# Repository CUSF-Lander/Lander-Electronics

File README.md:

# Lander-Electronics
Electronics for 25kg TVC hopper

### Creating new projects:
Open ```Template Project/Template Project.kicad_pro``` <br>
File>Save_As, then enter the new filename

### Adding New Symbols and Footprints
Adding footprints and symbols to the project specific library is the same as  usual. When connecting a footprint to a .stp file define a relative path to the file using ```${KIPRJMOD}/../Symbols and Footprints/3D Models/FILENAME.stp```

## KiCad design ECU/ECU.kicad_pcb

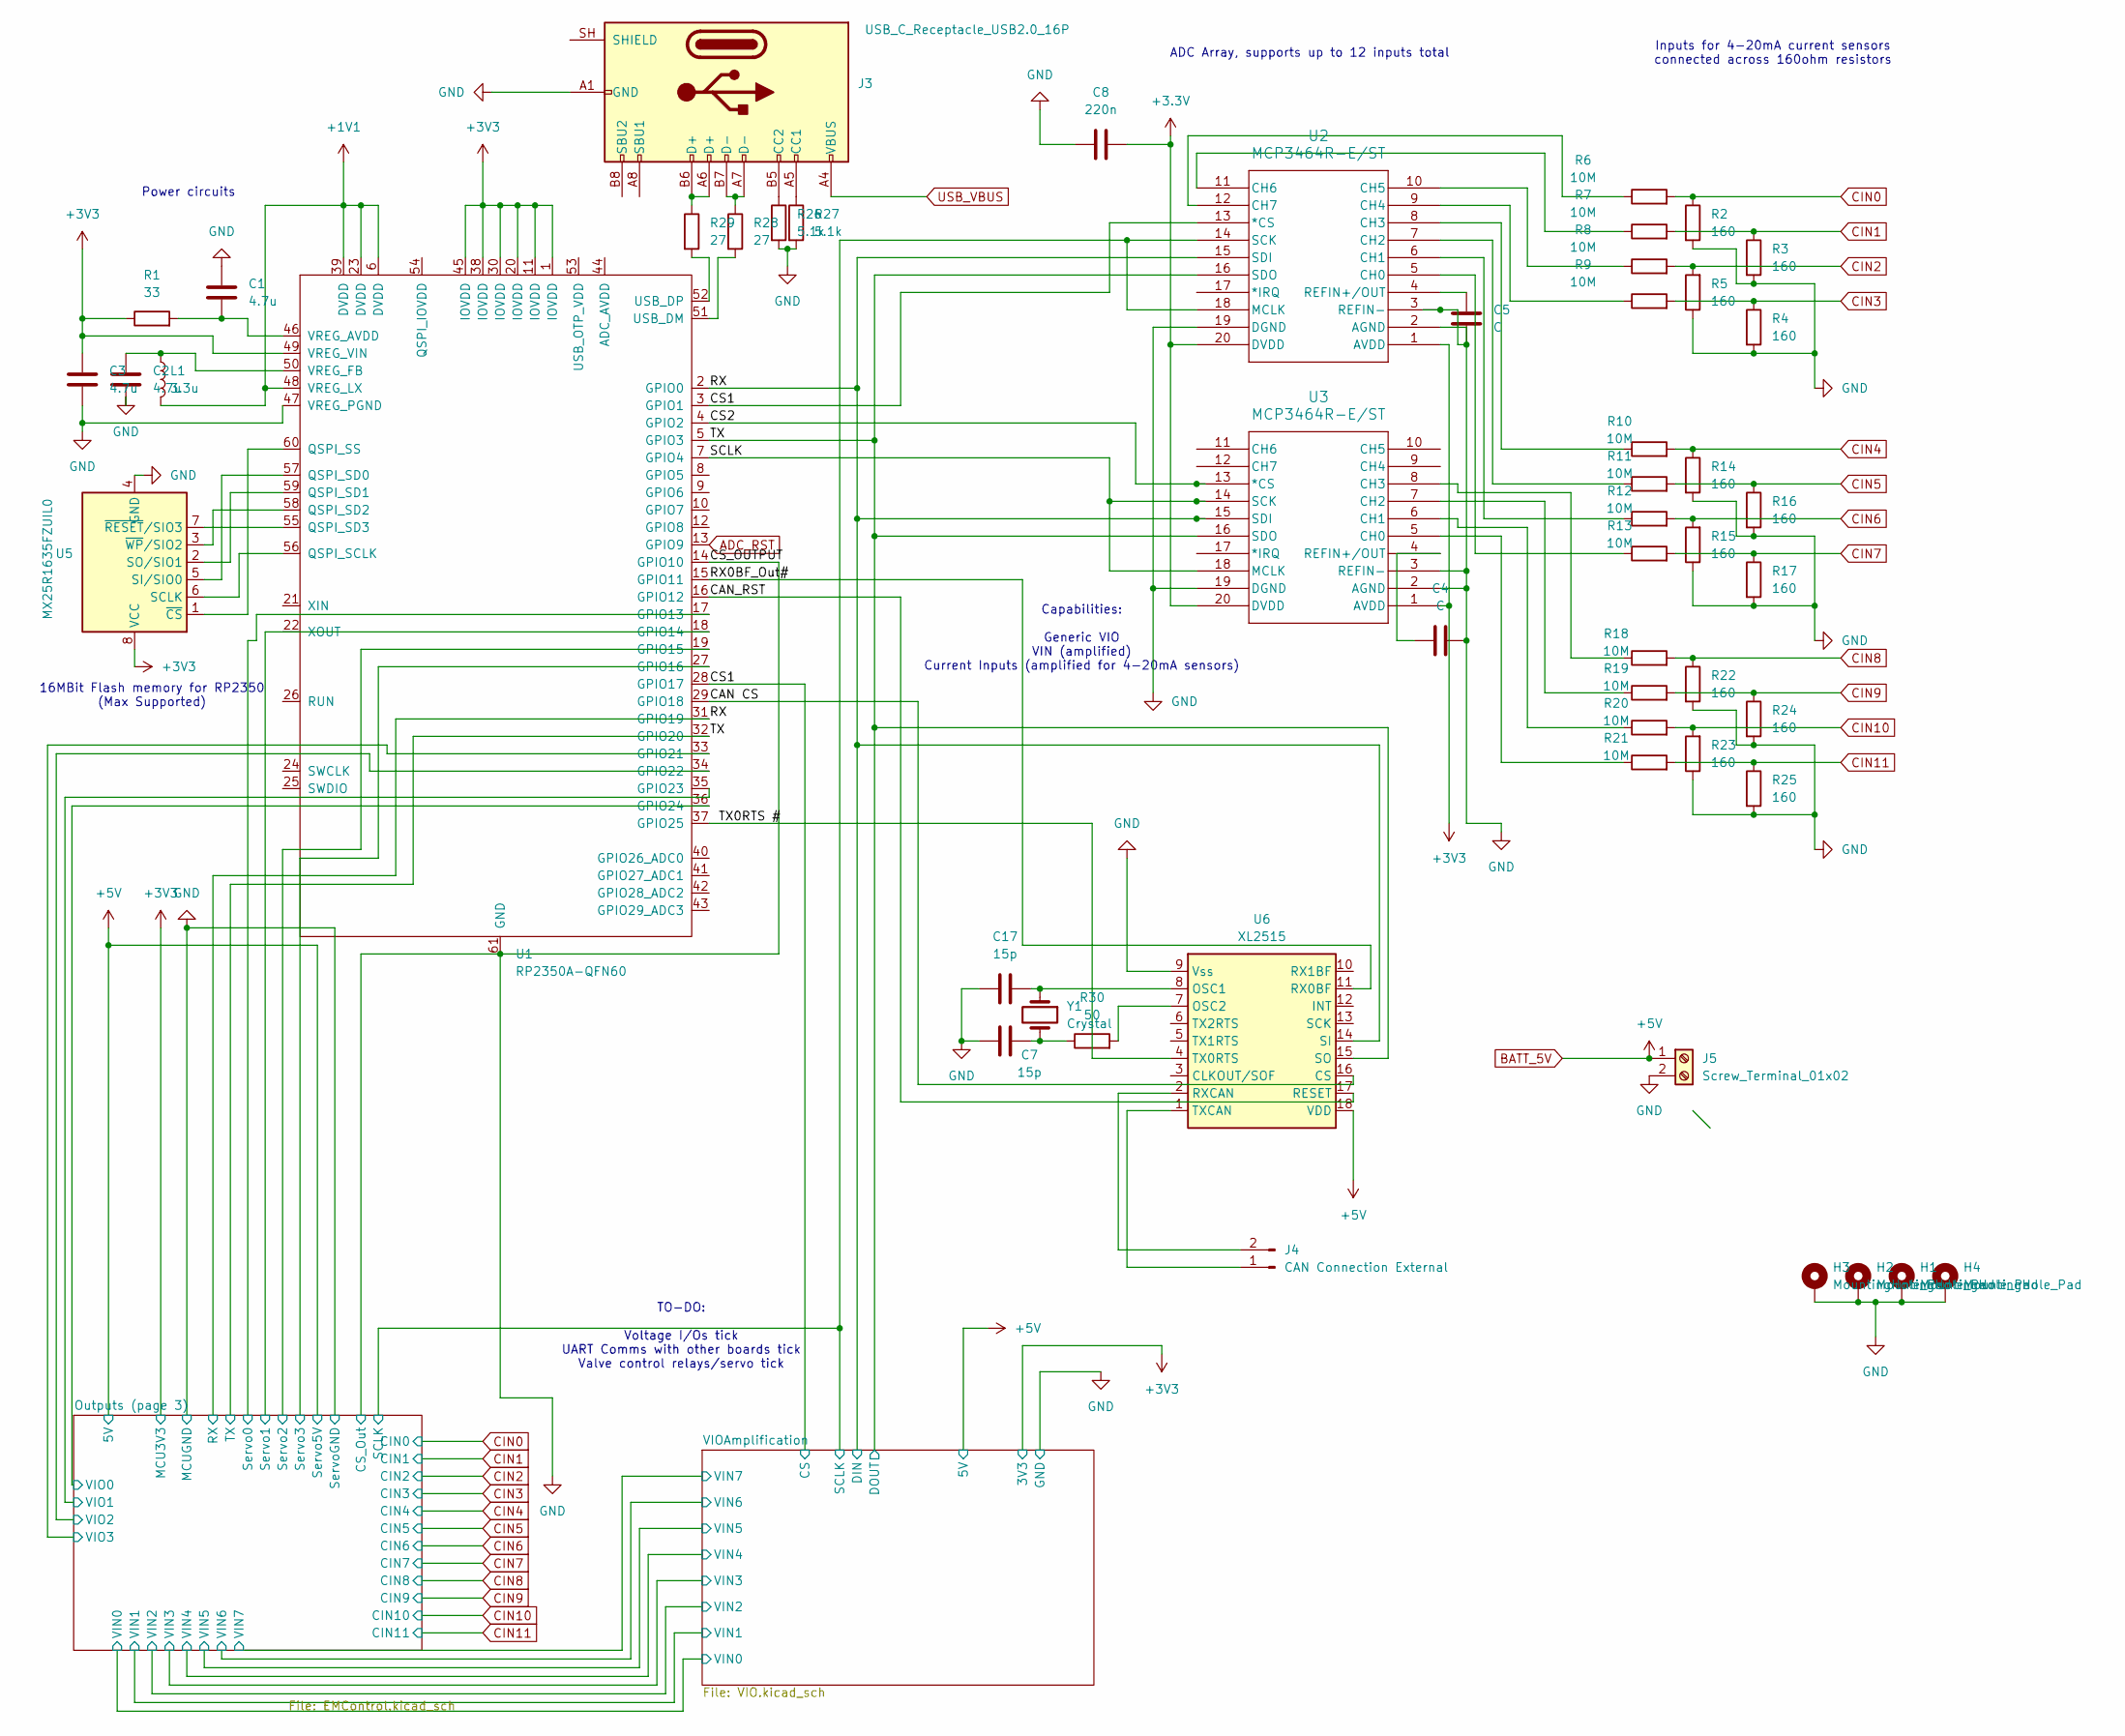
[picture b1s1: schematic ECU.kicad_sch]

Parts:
C1, C2, C3: 4.7u; C_1206_3216Metric_Pad1.33x1.80mm_HandSolder
C4, C5: C; C_1206_3216Metric
C7, C17: 15p; C_1206_3216Metric_Pad1.33x1.80mm_HandSolder
C8: 220n; C_0805_2012Metric_Pad1.18x1.45mm_HandSolder
H1, H2, H3, H4: MountingHole_Pad; MountingHole_3.2mm_M3_DIN965_Pad_TopBottom
J3: USB_C_Receptacle_USB2.0_16P; USB_C_Receptacle_HRO_TYPE-C-31-M-12
J4: CAN Connection External; PinHeader_1x02_P2.54mm_Vertical
J5: Screw_Terminal_01x02; TerminalBlock_Xinya_XY308-2.54-2P_1x02_P2.54mm_Horizontal
L1: 3.3u; L_0805_2012Metric_Pad1.05x1.20mm_HandSolder
R1: 33; R_1206_3216Metric_Pad1.30x1.75mm_HandSolder
R2, R3, R4, R5, R14, R15, R16, R17, R22, R23, R24, R25: 160; R_0805_2012Metric_Pad1.20x1.40mm_HandSolder
R6, R7, R8, R9, R10, R11, R12, R13, R18, R19, R20, R21: 10M; R_0805_2012Metric_Pad1.20x1.40mm_HandSolder
R26, R27: 5.1k; R_0805_2012Metric_Pad1.20x1.40mm_HandSolder
R28, R29: 27; R_0805_2012Metric_Pad1.20x1.40mm_HandSolder
R30: 50; R_1206_3216Metric_Pad1.30x1.75mm_HandSolder
U1: RP2350A-QFN60; QFN-60-1EP_7x7mm_P0.4mm_EP3.4x3.4mm
U2, U3: MCP3464R-E/ST; TSSOP-20_4.4x6.5mm_P0.4mm
U5: MX25R1635FZUIL0; JEITA_SOIC-8_3.9x4.9mm_P1.27mm
U6: XL2515; SOP-18_7.495x11.515mm_P1.27mm
Y1: Crystal; Crystal_HC49-U_Vertical

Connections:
+1V1: L1.2, U1.6 (DVDD), U1.23 (DVDD), U1.39 (DVDD), U1.48 (VREG_LX)
+3.3V: C8.2, U2.20 (DVDD), U3.20 (DVDD)
+3V3: C3.1, R1.1, U1.1 (IOVDD), U1.11 (IOVDD), U1.20 (IOVDD), U1.30 (IOVDD), U1.38 (IOVDD), U1.45 (IOVDD), U1.49 (VREG_VIN), U2.1 (AVDD), U3.1 (AVDD), U5.8 (VCC); also elsewhere on the board
/CAN CS: U1.29 (GPIO18), U6.16 (CS)
/CAN_RST: U1.16 (GPIO12), U6.17 (RESET)
/CS1: U1.3 (GPIO1), U1.28 (GPIO17), U2.13 (*CS); also elsewhere on the board
/CS2: U1.4 (GPIO2), U3.13 (*CS)
/Outputs (page 3)/SCLK: U2.14 (SCK), U2.18 (MCLK); also elsewhere on the board
/Outputs (page 3)/Servo0: U1.17 (GPIO13); also elsewhere on the board
/Outputs (page 3)/Servo1: U1.18 (GPIO14); also elsewhere on the board
/Outputs (page 3)/Servo2: U1.19 (GPIO15); also elsewhere on the board
/Outputs (page 3)/Servo3: U1.27 (GPIO16); also elsewhere on the board
/Outputs (page 3)/VIO0: U1.36 (GPIO24); also elsewhere on the board
/Outputs (page 3)/VIO1: U1.35 (GPIO23); also elsewhere on the board
/Outputs (page 3)/VIO2: U1.34 (GPIO22); also elsewhere on the board
/Outputs (page 3)/VIO3: U1.33 (GPIO21); also elsewhere on the board
/RX: U1.2 (GPIO0), U1.31 (GPIO19), U2.15 (SDI), U3.15 (SDI), U6.14 (SI); also elsewhere on the board
/RX0BF_Out#: U1.15 (GPIO11), U6.11 (RX0BF)
/SCLK: U1.7 (GPIO4), U3.14 (SCK), U3.18 (MCLK)
/TX: U1.5 (GPIO3), U1.32 (GPIO20), U2.16 (SDO), U3.16 (SDO), U6.15 (SO); also elsewhere on the board
/TX0RTS #: U1.37 (GPIO25), U6.4 (TX0RTS)
ADC_RST: U1.13 (GPIO9)
BATT_5V: J5.1, U6.18 (VDD); also elsewhere on the board
CIN0: R2.1, R6.2; also elsewhere on the board
CIN1: R3.1, R7.2; also elsewhere on the board
CIN2: R5.2, R8.2; also elsewhere on the board
CIN3: R4.1, R9.2; also elsewhere on the board
CIN4: R10.2, R14.1; also elsewhere on the board
CIN5: R11.2, R16.1; also elsewhere on the board
CIN6: R12.2, R15.2; also elsewhere on the board
CIN7: R13.2, R17.1; also elsewhere on the board
CIN8: R18.2, R22.1; also elsewhere on the board
CIN9: R19.2, R24.1; also elsewhere on the board
CIN10: R20.2, R23.2; also elsewhere on the board
CIN11: R21.2, R25.1; also elsewhere on the board
GND: C1.1, C2.2, C3.2, C4.1, C5.2, C7.1, C8.1, C17.1, H1.1 (1_1), H2.1 (1_1), H3.1 (1_1), H4.1 (1_1), J3.A1 (GND), J3.A12 (GND), J3.B1 (GND), J3.B12 (GND), J5.2, R2.2, R3.2, R4.2, R5.1, R14.2, R15.1, R16.2, R17.2, R22.2, R23.1, R24.2, R25.2, R26.2, R27.2, U1.14 (GPIO10), U1.47 (VREG_PGND), U1.61 (GND), U2.2 (AGND), U2.3 (REFIN-), U2.19 (DGND), U3.2 (AGND), U3.3 (REFIN-), U3.19 (DGND), U5.4 (GND), U6.9 (Vss); also elsewhere on the board
unnamed: C7.2, R30.1, Y1.2
unnamed: J3.A5 (CC1), R27.1
unnamed: J3.B5 (CC2), R26.1
unnamed: J3.A6 (D+), J3.B6 (D+), R29.1
unnamed: J3.A7 (D-), J3.B7 (D-), R28.1
unnamed: J4.1, U6.1 (TXCAN)
unnamed: J4.2, U6.2 (RXCAN)
unnamed: U1.56 (QSPI_SCLK), U5.6 (SCLK)
unnamed: U1.57 (QSPI_SD0), U5.5 (SI/SIO0)
unnamed: U1.59 (QSPI_SD1), U5.2 (SO/SIO1)
unnamed: U1.58 (QSPI_SD2), U5.3 (~WP/SIO2)
unnamed: U1.55 (QSPI_SD3), U5.7 (~RESET/SIO3)
unnamed: U1.60 (QSPI_SS), U5.1 (~CS)
unnamed: R28.2, U1.51 (USB_DM)
unnamed: R29.2, U1.52 (USB_DP)
unnamed: C1.2, R1.2, U1.46 (VREG_AVDD)
unnamed: C2.1, L1.1, U1.50 (VREG_FB)
unnamed: R13.1, U2.5 (CH0)
unnamed: R12.1, U2.6 (CH1)
unnamed: R11.1, U2.7 (CH2)
unnamed: R10.1, U2.8 (CH3)
unnamed: R9.1, U2.9 (CH4)
unnamed: R8.1, U2.10 (CH5)
unnamed: R7.1, U2.11 (CH6)
unnamed: R6.1, U2.12 (CH7)
unnamed: C5.1, U2.4 (REFIN+/OUT)
unnamed: R21.1, U3.5 (CH0)
unnamed: R20.1, U3.6 (CH1)
unnamed: R19.1, U3.7 (CH2)
unnamed: R18.1, U3.8 (CH3)
unnamed: C4.2, U3.4 (REFIN+/OUT)
unnamed: C17.2, U6.8 (OSC1), Y1.1
unnamed: R30.2, U6.7 (OSC2)
USB_VBUS: J3.A4 (VBUS), J3.A9 (VBUS), J3.B4 (VBUS), J3.B9 (VBUS); also elsewhere on the board

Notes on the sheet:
ADC Array, supports up to 12 inputs total
Capabilities: Generic VIO VIN (amplified) Current Inputs (amplified for 4-20mA sensors)
Power circuits
Inputs for 4-20mA current sensors connected across 160ohm resistors
TO-DO: Voltage I/Os tick UART Comms with other boards tick Valve control relays/servo tick
16MBit Flash memory for RP2350 (Max Supported)

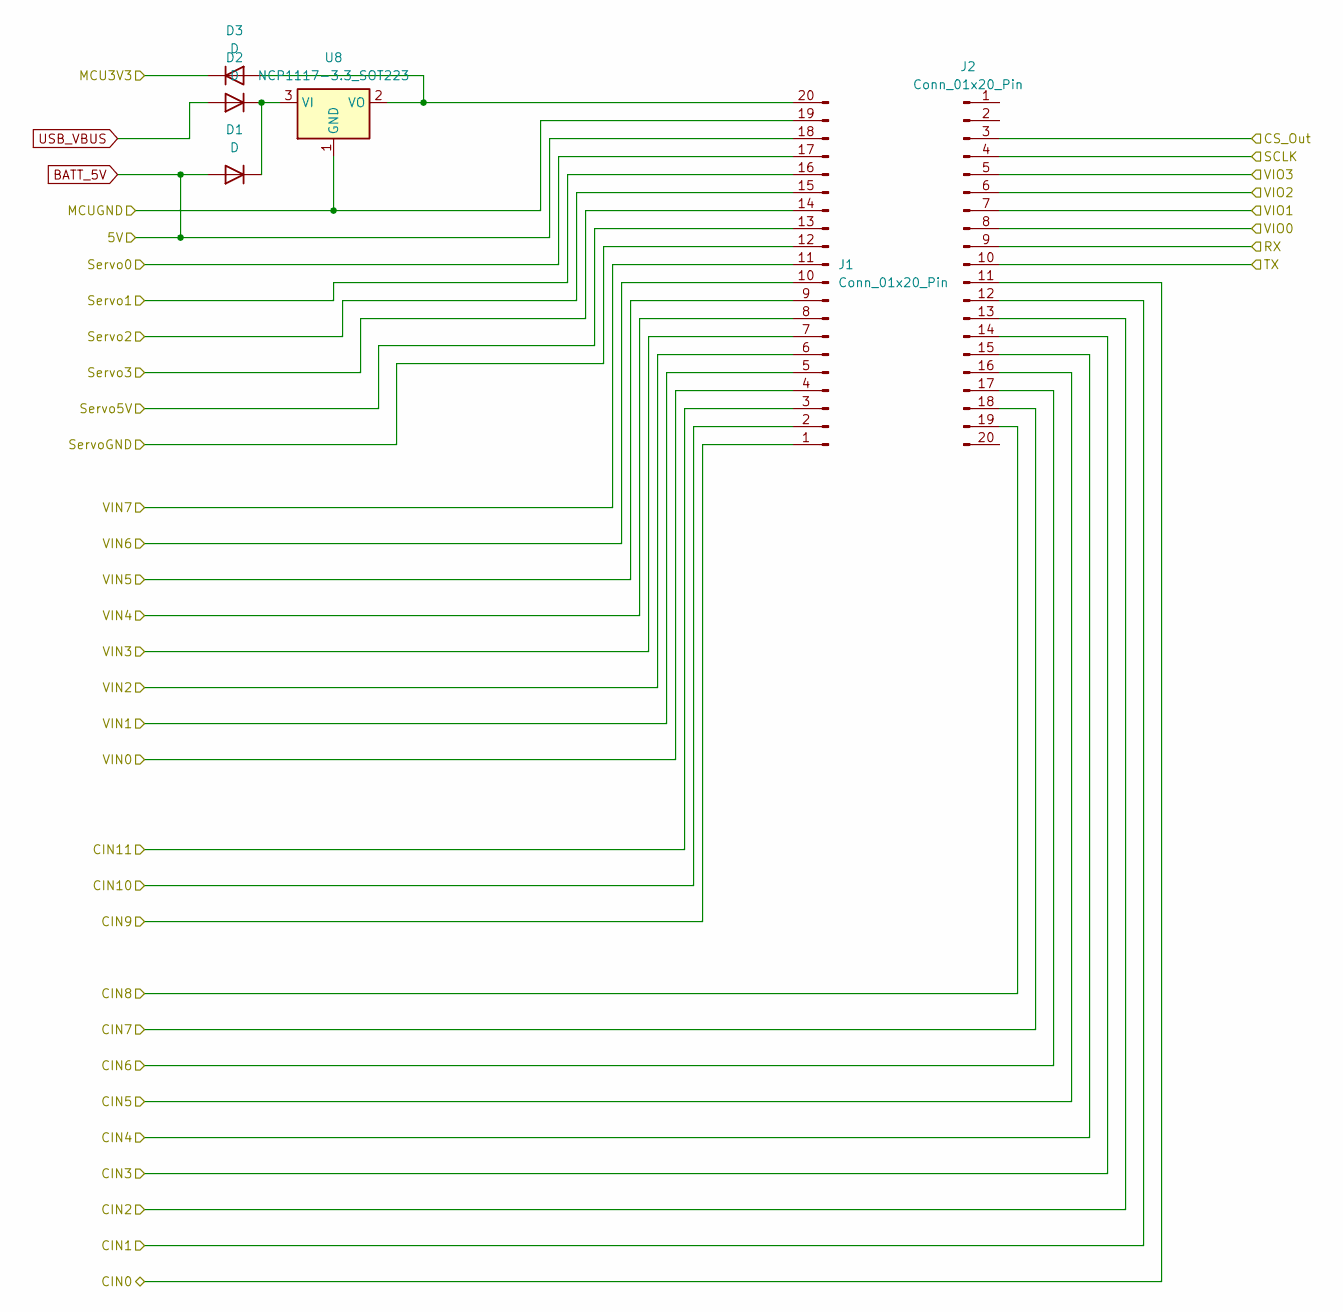
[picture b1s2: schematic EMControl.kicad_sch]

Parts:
D1, D2, D3: D; D_1206_3216Metric_Pad1.42x1.75mm_HandSolder
J1, J2: Conn_01x20_Pin; PinHeader_1x20_P1.00mm_Vertical
U8: NCP1117-3.3_SOT223; SOT-223-3_TabPin2

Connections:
+3V3: D3.1 (K); also elsewhere on the board
/Outputs (page 3)/SCLK: J2.4; also elsewhere on the board
/Outputs (page 3)/Servo0: J1.17; also elsewhere on the board
/Outputs (page 3)/Servo1: J1.16; also elsewhere on the board
/Outputs (page 3)/Servo2: J1.15; also elsewhere on the board
/Outputs (page 3)/Servo3: J1.14; also elsewhere on the board
/Outputs (page 3)/VIN0: J1.4; also elsewhere on the board
/Outputs (page 3)/VIN1: J1.5; also elsewhere on the board
/Outputs (page 3)/VIN2: J1.6; also elsewhere on the board
/Outputs (page 3)/VIN3: J1.7; also elsewhere on the board
/Outputs (page 3)/VIN4: J1.8; also elsewhere on the board
/Outputs (page 3)/VIN5: J1.9; also elsewhere on the board
/Outputs (page 3)/VIN6: J1.10; also elsewhere on the board
/Outputs (page 3)/VIN7: J1.11; also elsewhere on the board
/Outputs (page 3)/VIO0: J2.8; also elsewhere on the board
/Outputs (page 3)/VIO1: J2.7; also elsewhere on the board
/Outputs (page 3)/VIO2: J2.6; also elsewhere on the board
/Outputs (page 3)/VIO3: J2.5; also elsewhere on the board
/RX: J2.9; also elsewhere on the board
/TX: J2.10; also elsewhere on the board
BATT_5V: D1.2 (A), J1.13, J1.18; also elsewhere on the board
CIN0: J2.11; also elsewhere on the board
CIN1: J2.12; also elsewhere on the board
CIN2: J2.13; also elsewhere on the board
CIN3: J2.14; also elsewhere on the board
CIN4: J2.15; also elsewhere on the board
CIN5: J2.16; also elsewhere on the board
CIN6: J2.17; also elsewhere on the board
CIN7: J2.18; also elsewhere on the board
CIN8: J2.19; also elsewhere on the board
CIN9: J1.1; also elsewhere on the board
CIN10: J1.2; also elsewhere on the board
CIN11: J1.3; also elsewhere on the board
GND: J1.12, J1.19, J2.3, U8.1 (GND); also elsewhere on the board
unnamed: D1.1 (K), D2.1 (K), U8.3 (VI)
unnamed: D3.2 (A), J1.20, U8.2 (VO)
USB_VBUS: D2.2 (A); also elsewhere on the board

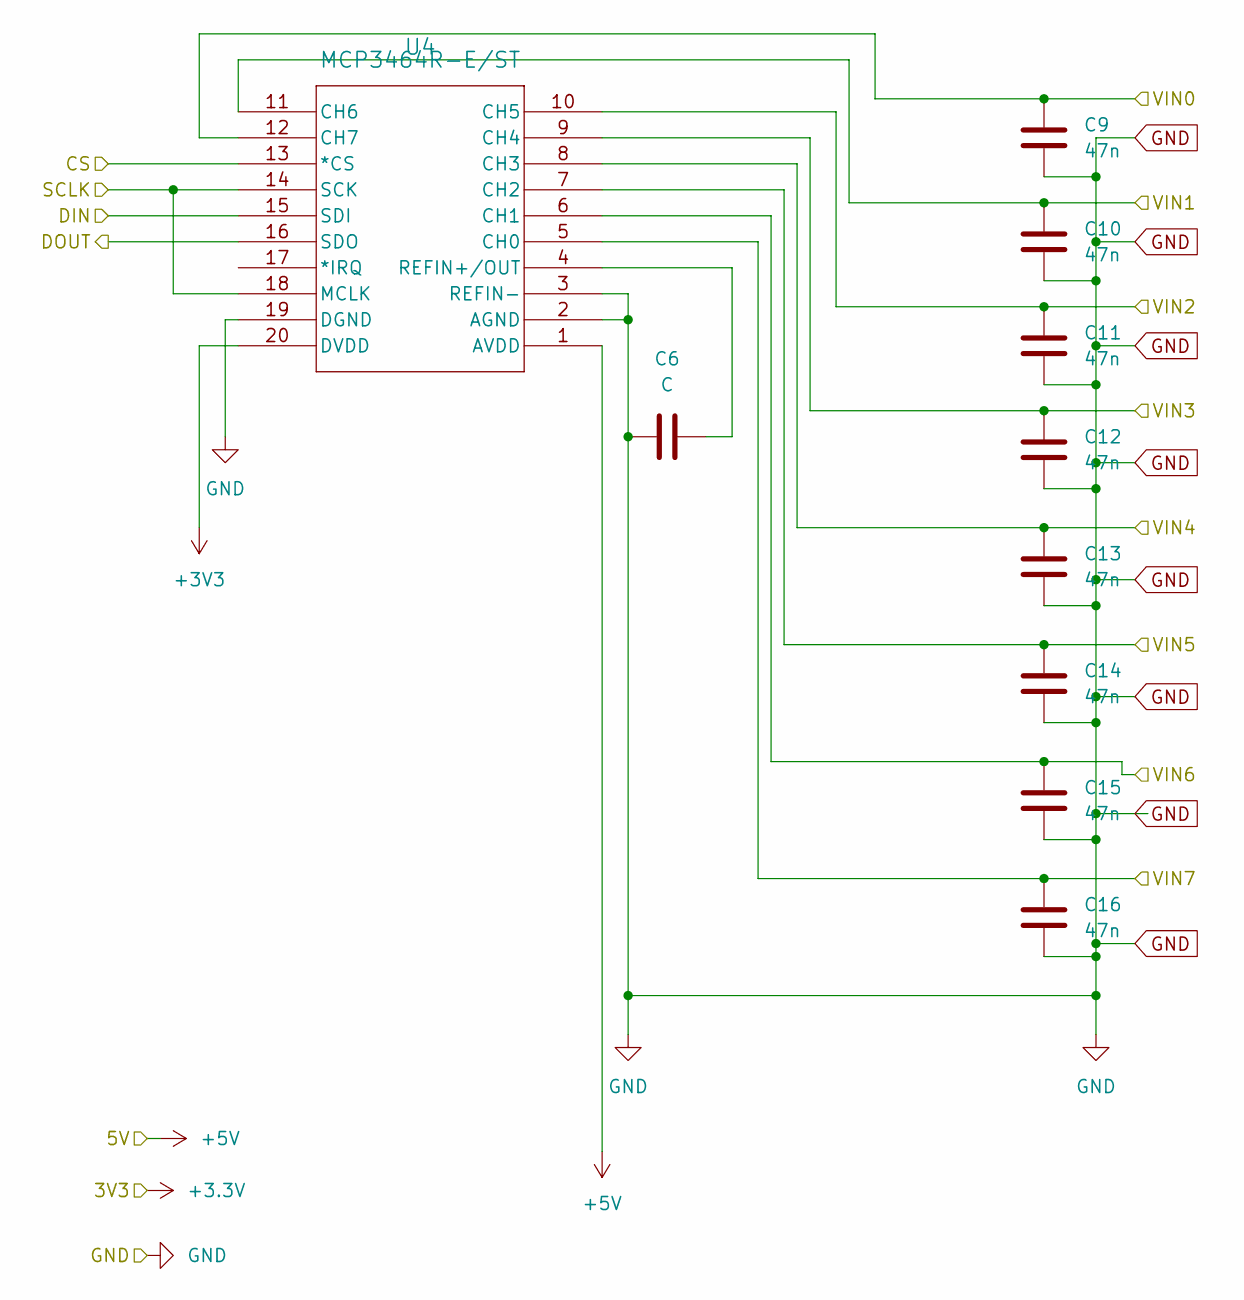
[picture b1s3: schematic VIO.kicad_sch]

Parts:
C6: C; C_0805_2012Metric
C9, C10, C11, C12, C13, C14, C15, C16: 47n; C_1206_3216Metric_Pad1.33x1.80mm_HandSolder
U4: MCP3464R-E/ST; TSSOP-20_4.4x6.5mm_P0.4mm

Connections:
+3V3: U4.20 (DVDD); also elsewhere on the board
/CS1: U4.13 (*CS); also elsewhere on the board
/Outputs (page 3)/SCLK: U4.14 (SCK), U4.18 (MCLK); also elsewhere on the board
/Outputs (page 3)/VIN0: C9.1, U4.12 (CH7); also elsewhere on the board
/Outputs (page 3)/VIN1: C10.1, U4.11 (CH6); also elsewhere on the board
/Outputs (page 3)/VIN2: C11.1, U4.10 (CH5); also elsewhere on the board
/Outputs (page 3)/VIN3: C12.1, U4.9 (CH4); also elsewhere on the board
/Outputs (page 3)/VIN4: C13.1, U4.8 (CH3); also elsewhere on the board
/Outputs (page 3)/VIN5: C14.1, U4.7 (CH2); also elsewhere on the board
/Outputs (page 3)/VIN6: C15.1, U4.6 (CH1); also elsewhere on the board
/Outputs (page 3)/VIN7: C16.1, U4.5 (CH0); also elsewhere on the board
/RX: U4.15 (SDI); also elsewhere on the board
/TX: U4.16 (SDO); also elsewhere on the board
BATT_5V: U4.1 (AVDD); also elsewhere on the board
GND: C6.2, C9.2, C10.2, C11.2, C12.2, C13.2, C14.2, C15.2, C16.2, U4.2 (AGND), U4.3 (REFIN-), U4.19 (DGND); also elsewhere on the board
unnamed: C6.1, U4.4 (REFIN+/OUT)

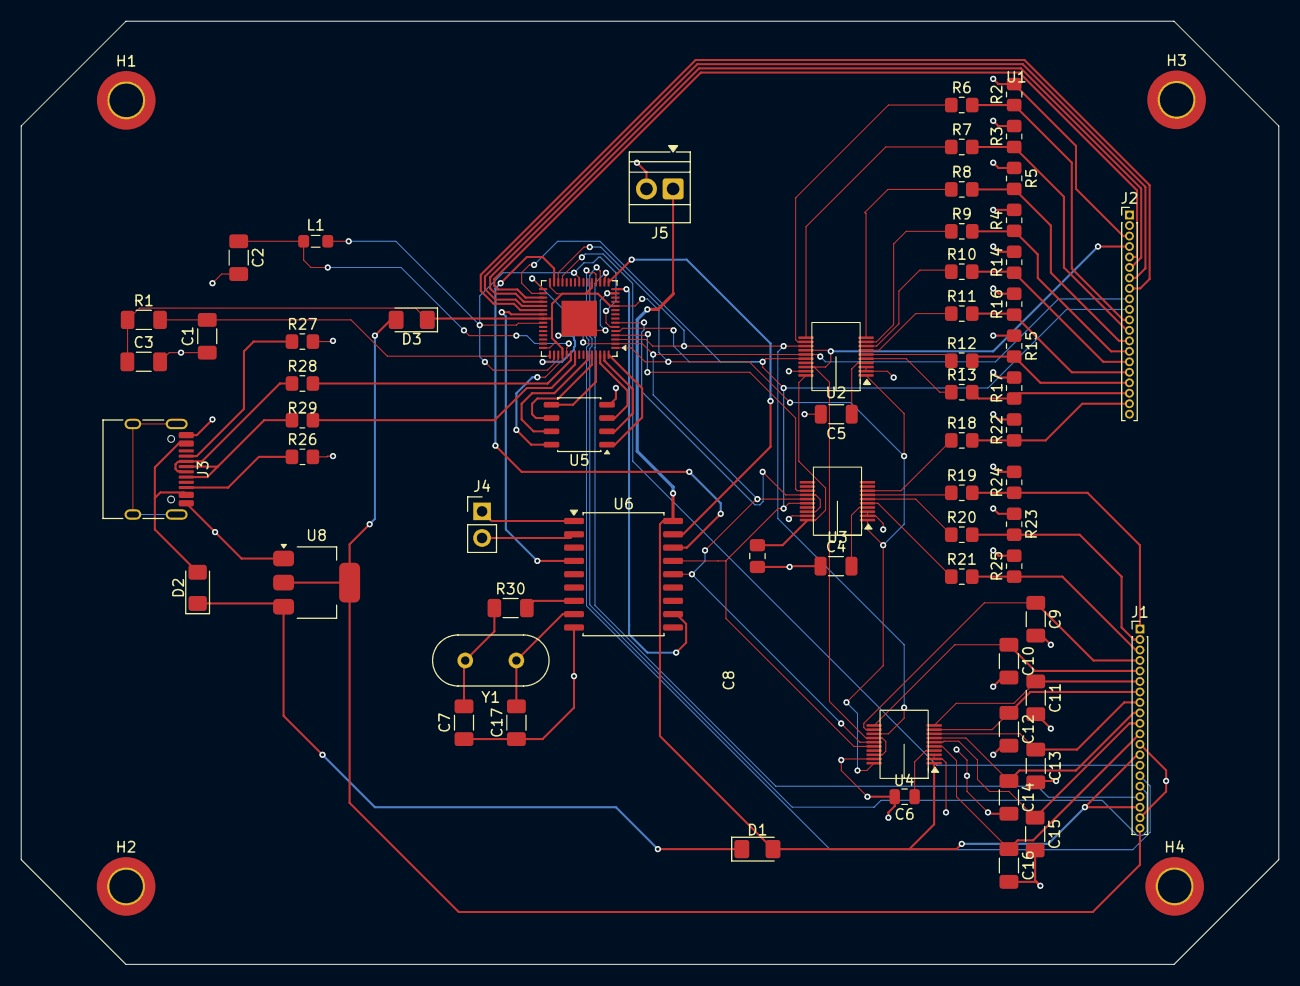
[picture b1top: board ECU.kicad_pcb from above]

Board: 2 copper layers, 120.0 x 90.0 mm, 68 parts (0 on the bottom side), 80 nets.

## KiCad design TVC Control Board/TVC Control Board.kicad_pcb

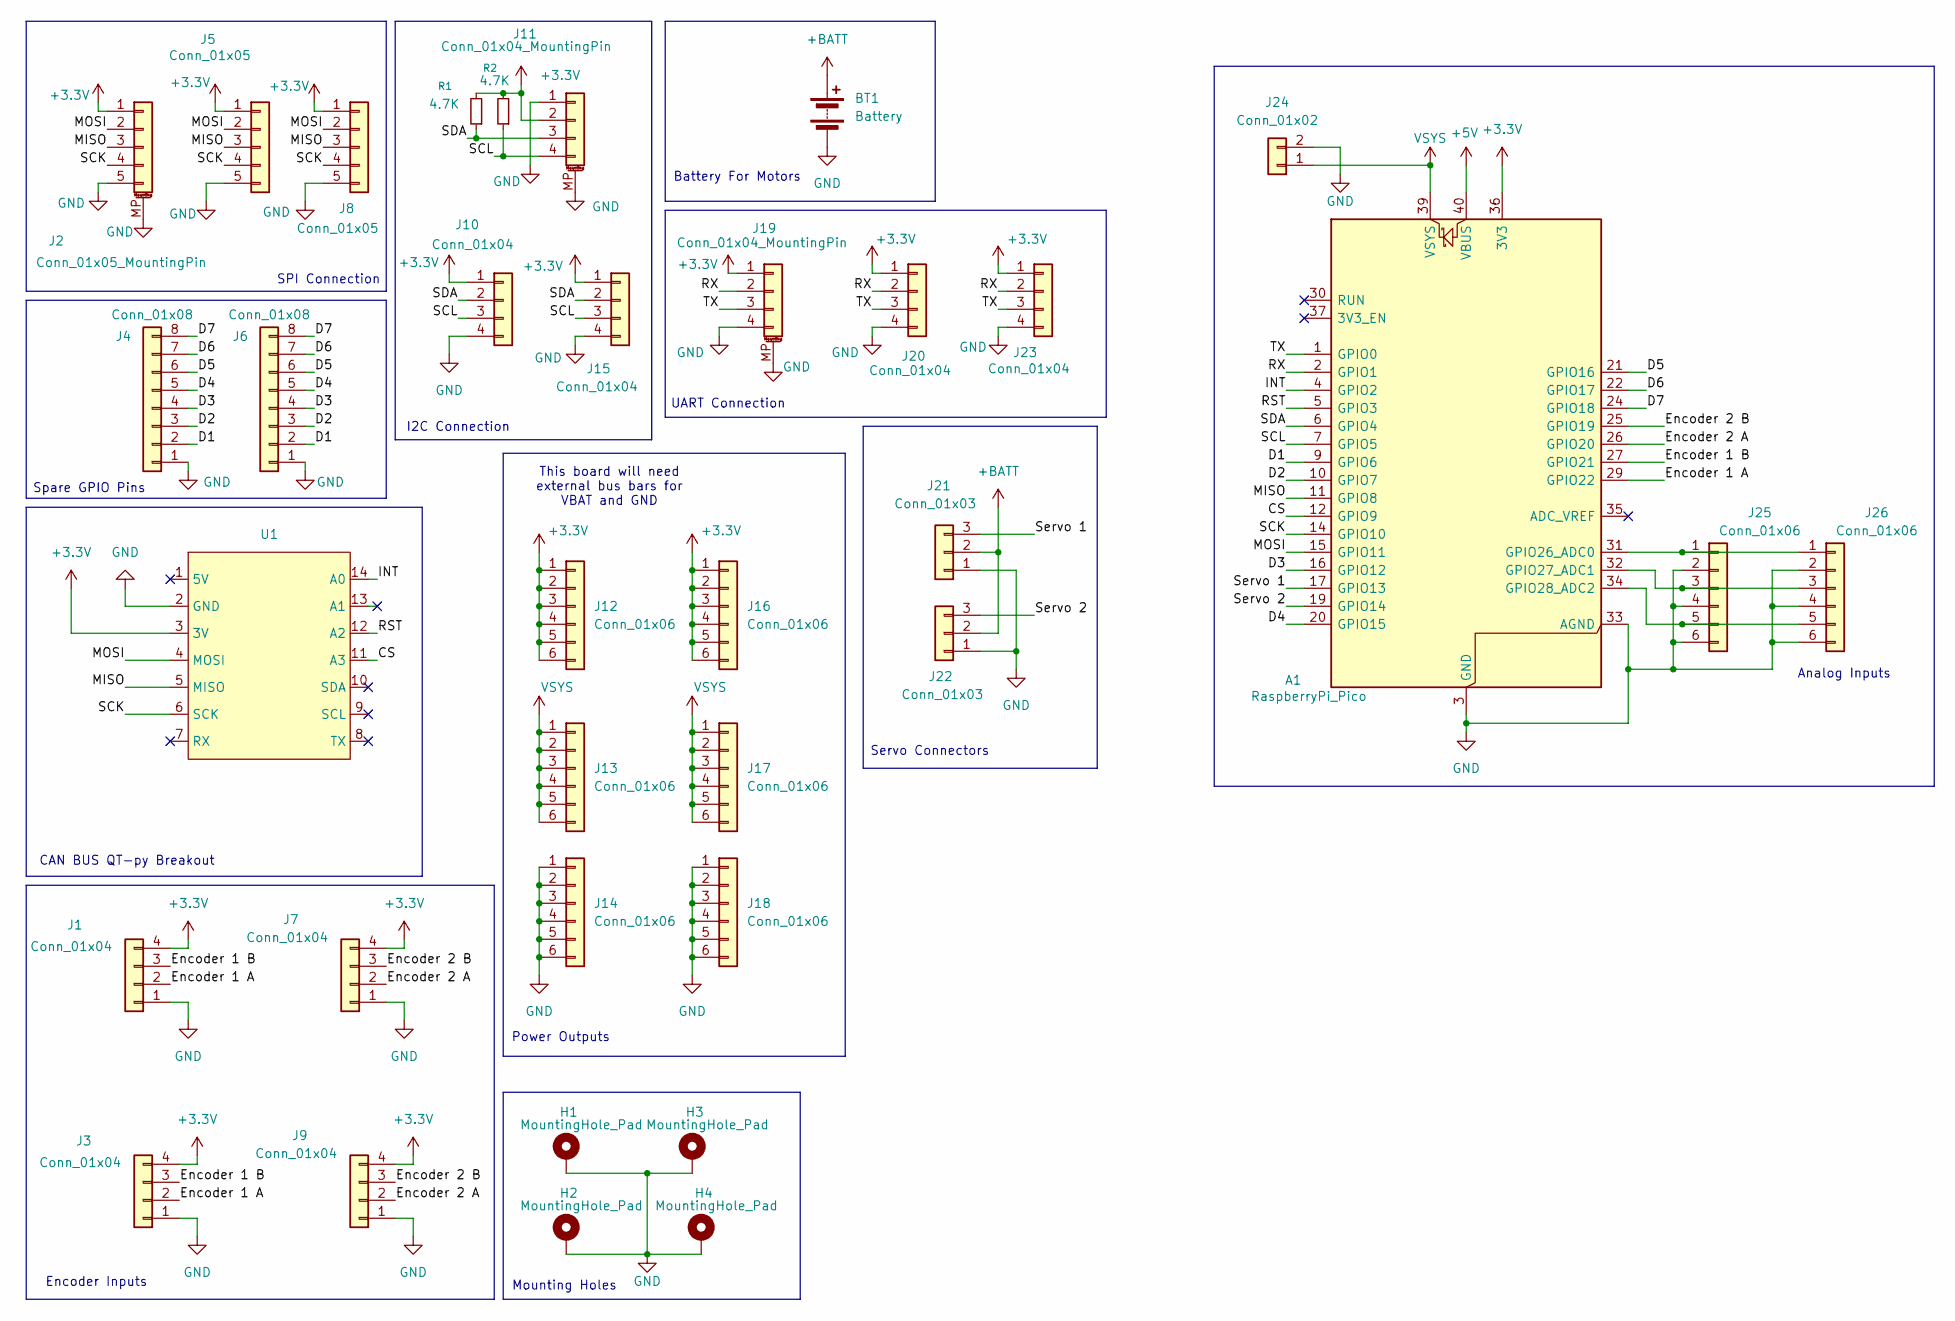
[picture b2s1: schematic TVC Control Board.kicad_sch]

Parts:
A1: RaspberryPi_Pico; RaspberryPi_Pico_Common_Unspecified
BT1: Battery; TVC Board Battery Connector
H1, H2, H3, H4: MountingHole_Pad; MountingHole_3.2mm_M3_Pad
J1, J3, J7, J9, J10, J15, J20, J23: Conn_01x04; PinHeader_1x04_P2.54mm_Vertical
J2: Conn_01x05_MountingPin; JST_SH_SM05B-SRSS-TB_1x05-1MP_P1.00mm_Horizontal
J4, J6: Conn_01x08; PinHeader_1x08_P2.54mm_Vertical
J5, J8: Conn_01x05; PinHeader_1x05_P2.54mm_Vertical
J11, J19: Conn_01x04_MountingPin; JST_SH_SM04B-SRSS-TB_1x04-1MP_P1.00mm_Horizontal
J12, J13, J14, J16, J17, J18, J25, J26: Conn_01x06; PinHeader_1x06_P2.54mm_Vertical
J21, J22: Conn_01x03; PinHeader_1x03_P2.54mm_Vertical
J24: Conn_01x02; JST_PH_B2B-PH-K_1x02_P2.00mm_Vertical
R1, R2: 4.7K; R_0805_2012Metric_Pad1.20x1.40mm_HandSolder
U1: MODULE_ADAFRUIT_QT_PY

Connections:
+3.3V: A1.36 (3V3), J1.4, J2.1, J3.4, J5.1, J7.4, J8.1, J9.4, J10.1, J11.2, J12.1, J12.2, J12.3, J12.4, J12.5, J12.6, J15.1, J16.1, J16.2, J16.3, J16.4, J16.5, J16.6, J19.1, J20.1, J23.1, R1.2, R2.2, U1.3 (3V)
+5V: A1.40 (VBUS)
+BATT: BT1.1 (+), J21.2, J22.2
/CS: A1.12 (GPIO9), U1.11 (A3)
/D1: A1.9 (GPIO6), J4.2, J6.2
/D2: A1.10 (GPIO7), J4.3, J6.3
/D3: A1.16 (GPIO12), J4.4, J6.4
/D4: A1.20 (GPIO15), J4.5, J6.5
/D5: A1.21 (GPIO16), J4.6, J6.6
/D6: A1.22 (GPIO17), J4.7, J6.7
/D7: A1.24 (GPIO18), J4.8, J6.8
/Encoder 1 A: A1.29 (GPIO22), J1.2, J3.2
/Encoder 1 B: A1.27 (GPIO21), J1.3, J3.3
/Encoder 2 A: A1.26 (GPIO20), J7.2, J9.2
/Encoder 2 B: A1.25 (GPIO19), J7.3, J9.3
/INT: A1.4 (GPIO2), U1.14 (A0)
/MISO: A1.11 (GPIO8), J2.3, J5.3, J8.3, U1.5 (MISO)
/MOSI: A1.15 (GPIO11), J2.2, J5.2, J8.2, U1.4 (MOSI)
/RST: A1.5 (GPIO3), U1.12 (A2)
/RX: A1.2 (GPIO1), J19.2, J20.2, J23.2
/SCK: A1.14 (GPIO10), J2.4, J5.4, J8.4, U1.6 (SCK)
/SCL: A1.7 (GPIO5), J10.3, J11.4, J15.3, R2.1
/SDA: A1.6 (GPIO4), J10.2, J11.3, J15.2, R1.1
/Servo 1: A1.17 (GPIO13), J21.3
/Servo 2: A1.19 (GPIO14), J22.3
/TX: A1.1 (GPIO0), J19.3, J20.3, J23.3
GND: A1.3 (GND), A1.8 (GND), A1.13 (GND), A1.18 (GND), A1.23 (GND), A1.28 (GND), A1.33 (AGND), A1.38 (GND), BT1.2 (-), H1.1 (1_1), H2.1 (1_1), H3.1 (1_1), H4.1 (1_1), J1.1, J2.5, J2.MP (MountPin), J3.1, J4.1, J5.5, J6.1, J7.1, J8.5, J9.1, J10.4, J11.1, J11.MP (MountPin), J14.1, J14.2, J14.3, J14.4, J14.5, J14.6, J15.4, J18.1, J18.2, J18.3, J18.4, J18.5, J18.6, J19.4, J19.MP (MountPin), J20.4, J21.1, J22.1, J23.4, J24.2, J25.2, J25.4, J25.6, J26.2, J26.4, J26.6, U1.2 (GND)
unnamed: A1.31 (GPIO26_ADC0), J25.1, J26.1
unnamed: A1.32 (GPIO27_ADC1), J25.3, J26.3
unnamed: A1.34 (GPIO28_ADC2), J25.5, J26.5
VSYS: A1.39 (VSYS), J13.1, J13.2, J13.3, J13.4, J13.5, J13.6, J17.1, J17.2, J17.3, J17.4, J17.5, J17.6, J24.1

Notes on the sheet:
UART Connection
Encoder Inputs
SPI Connection
Mounting Holes
Spare GPIO Pins
Servo Connectors
CAN BUS QT-py Breakout
Analog Inputs
Power Outputs
This board will need external bus bars for VBAT and GND
Battery For Motors
I2C Connection

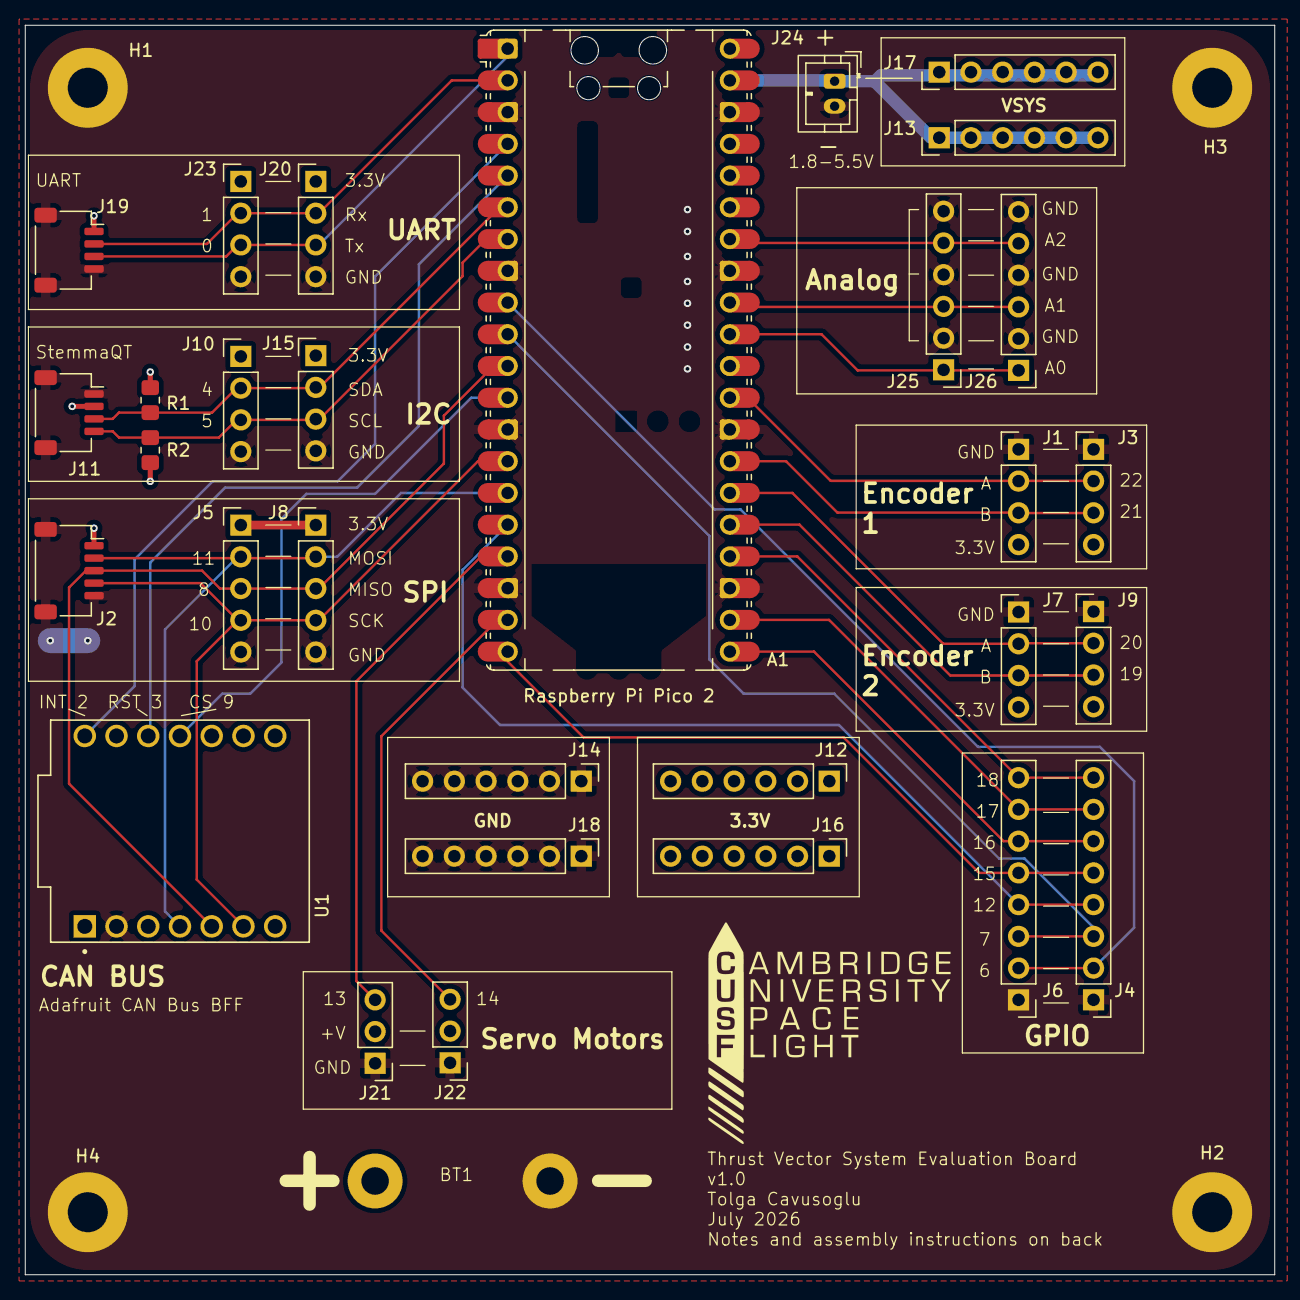
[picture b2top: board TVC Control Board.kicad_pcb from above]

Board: 2 copper layers, 100.0 x 100.0 mm, 35 parts (0 on the bottom side), 30 nets.

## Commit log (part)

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2026-04-10 Create Project Structure
2026-04-30 add .gitignore
2026-04-30 Added sensor datasheets
2026-04-30 Added barometric pressure sensors and IMUs to footprint and symbol library
2026-05-03 Added Voltage IO sheet, and provisions for the servo, relay, and solenoid control electronics
2026-05-09 finished ECU
2026-05-09 Integrate Sensor for Flight Computer
2026-05-10 Use heirarchical sheets for flight computer and add power supply filter capacitors
2026-05-10 VIO added
2026-05-10 small changes
2026-05-16 Initial Schematic
2026-05-24 Preliminary PCB Layout
2026-05-30 Schematic improvements and preliminary routing
2026-05-31 Finalize schematic and routing
